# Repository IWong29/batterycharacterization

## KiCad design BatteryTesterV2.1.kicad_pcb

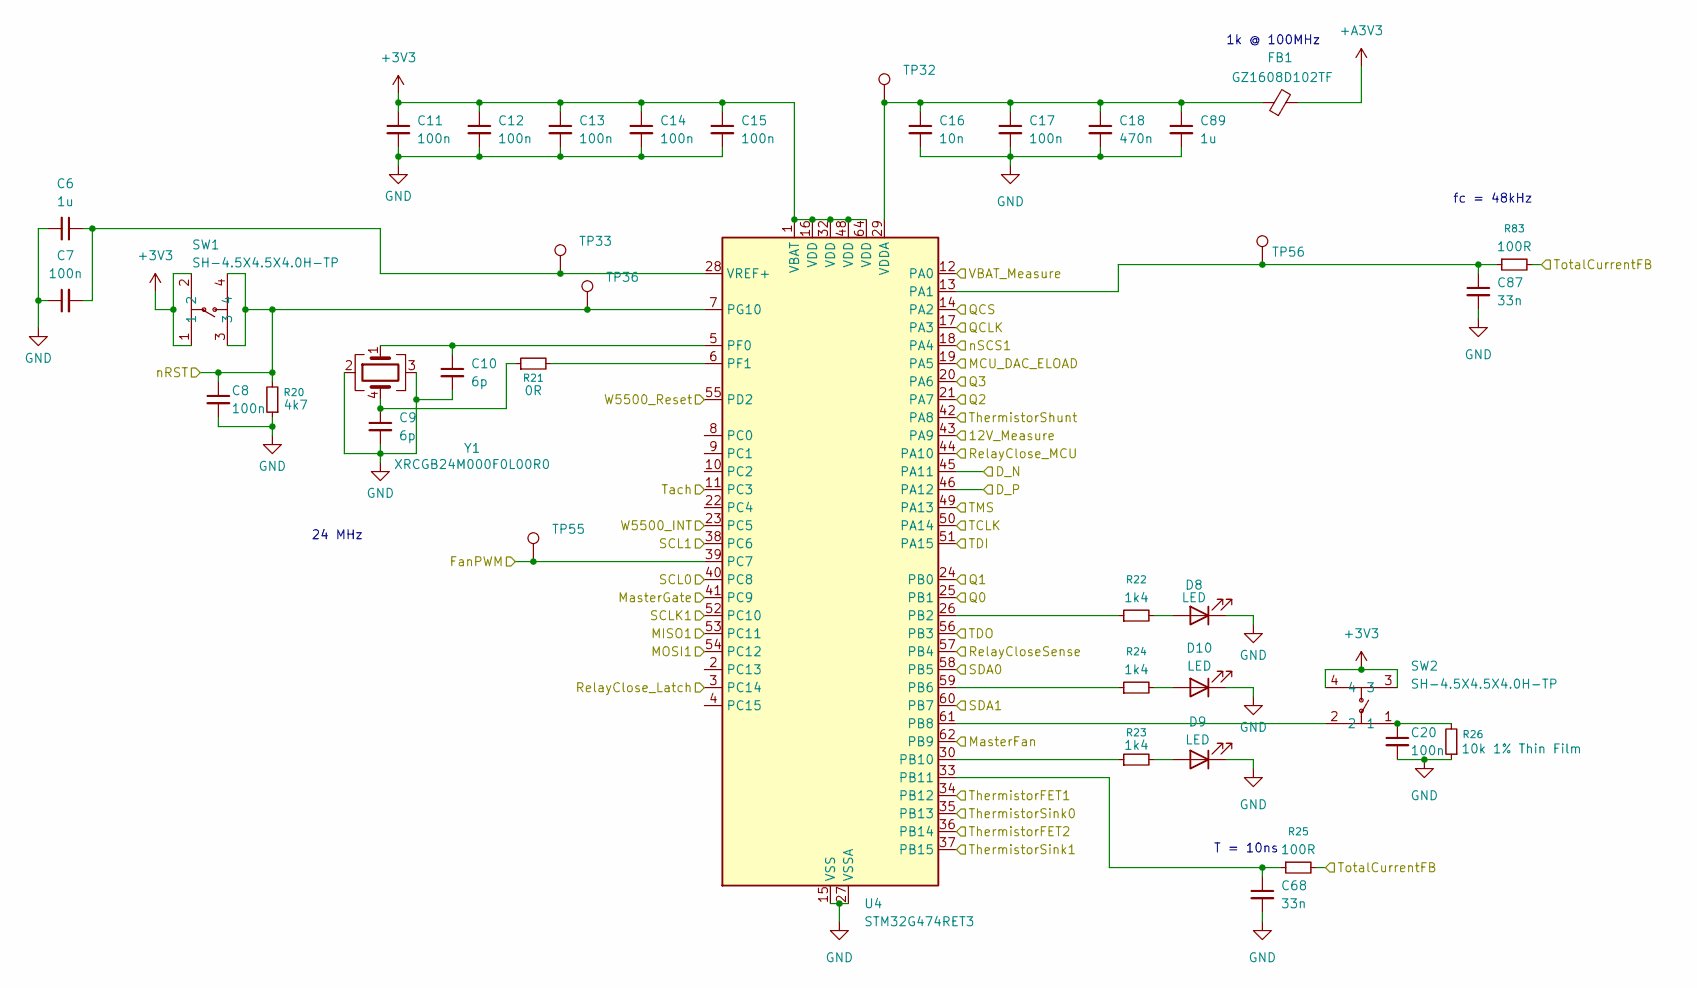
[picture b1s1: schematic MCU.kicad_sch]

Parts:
C6, C89: 1u; C_0603_1608Metric
C7, C11, C12, C13, C14, C15, C17: 100n; C_0603_1608Metric
C8, C20: 100n; C_0402_1005Metric
C9, C10: 6p; C_0402_1005Metric
C16: 10n; C_0603_1608Metric
C18: 470n; C_0603_1608Metric
C68, C87: 33n; C_0603_1608Metric
D8, D9, D10: LED; D_0603_1608Metric
FB1: GZ1608D102TF; C_0603_1608Metric
R20: 4k7; R_0603_1608Metric
R21: 0R; R_0603_1608Metric
R22, R23, R24: 1k4; R_0603_1608Metric
R25, R83: 100R; R_0603_1608Metric
R26: 10k 1% Thin Film; R_0603_1608Metric
SW1, SW2: SH-4.5X4.5X4.0H-TP; SW-SMD_4P-SH-4.5X4.5X4.0H-TP; MPN SH-4.5x4.5x4.0H-TP; LCSC Part C52092029
TP32, TP33, TP36, TP55, TP56: TestPoint; TestPoint_Pad_D1.0mm
U4: STM32G474RET3; LQFP-64_10x10mm_P0.5mm
Y1: XRCGB24M000F0L00R0

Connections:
+3V3: C11.1, C12.1, C13.1, C14.1, C15.1, SW1.1, SW1.2, SW2.3, SW2.4, U4.1 (VBAT), U4.16 (VDD), U4.32 (VDD), U4.48 (VDD), U4.64 (VDD); also elsewhere on the board
+A3V3: FB1.2; also elsewhere on the board
/BatteryV2/MasterGate: U4.41 (PC9); also elsewhere on the board
/BatteryV2/RelayCloseOut: U4.57 (PB4); also elsewhere on the board
/BatteryV2/RelayClose_Latch: U4.3 (PC14); also elsewhere on the board
/BatteryV2/RelayClose_MCU: U4.44 (PA10); also elsewhere on the board
/Connectors/D_N: U4.45 (PA11); also elsewhere on the board
/Connectors/D_P: U4.46 (PA12); also elsewhere on the board
/Connectors/Fan_PWM: TP55.1, U4.39 (PC7); also elsewhere on the board
/Connectors/MasterFan: U4.62 (PB9); also elsewhere on the board
/Connectors/TCLK: U4.50 (PA14); also elsewhere on the board
/Connectors/TDI: U4.51 (PA15); also elsewhere on the board
/Connectors/TDO: U4.56 (PB3); also elsewhere on the board
/Connectors/TMS: U4.49 (PA13); also elsewhere on the board
/Connectors/Tach: U4.11 (PC3); also elsewhere on the board
/Connectors/nRST: C8.1, R20.2, SW1.3, SW1.4, TP36.1, U4.7 (PG10); also elsewhere on the board
/ELOAD/MCU_DAC_ELOAD: U4.19 (PA5); also elsewhere on the board
/ELOAD/ThermistorSink0: U4.35 (PB13); also elsewhere on the board
/ELOAD/ThermistorSink1: U4.37 (PB15); also elsewhere on the board
/MCU/12V_Measure: U4.43 (PA9); also elsewhere on the board
/MCU/MISO1: U4.53 (PC11); also elsewhere on the board
/MCU/MOSI1: U4.54 (PC12); also elsewhere on the board
/MCU/Q0: U4.25 (PB1); also elsewhere on the board
/MCU/Q1: U4.24 (PB0); also elsewhere on the board
/MCU/Q2: U4.21 (PA7); also elsewhere on the board
/MCU/Q3: U4.20 (PA6); also elsewhere on the board
/MCU/QCLK: U4.17 (PA3); also elsewhere on the board
/MCU/QCS: U4.14 (PA2); also elsewhere on the board
/MCU/SCL0: U4.40 (PC8)
/MCU/SCL1: U4.38 (PC6); also elsewhere on the board
/MCU/SCLK1: U4.52 (PC10); also elsewhere on the board
/MCU/SDA0: U4.58 (PB5)
/MCU/SDA1: U4.60 (PB7); also elsewhere on the board
/MCU/ThermistorFET1: U4.34 (PB12); also elsewhere on the board
/MCU/ThermistorFET2: U4.36 (PB14); also elsewhere on the board
/MCU/ThermistorShunt: U4.42 (PA8); also elsewhere on the board
/MCU/TotalCurrentFB: R25.2, R83.2; also elsewhere on the board
/MCU/VBAT_Measure: U4.12 (PA0); also elsewhere on the board
/MCU/W5500_INT: U4.23 (PC5); also elsewhere on the board
/MCU/W5500_Reset: U4.55 (PD2); also elsewhere on the board
/MCU/nSCS1: U4.18 (PA4); also elsewhere on the board
GND: C6.2, C7.1, C8.2, C9.2, C10.2, C11.2, C12.2, C13.2, C14.2, C15.2, C16.2, C17.2, C18.2, C20.2, C68.2, C87.2, C89.2, D8.1 (K), D9.1 (K), D10.1 (K), R20.1, R26.1, U4.15 (VSS), U4.27 (VSSA), U4.31 (VSS), U4.47 (VSS), U4.63 (VSS), Y1.2, Y1.3; also elsewhere on the board
unnamed: C9.1, R21.1, Y1.4
unnamed: C20.1, R26.2, SW2.1
unnamed: D8.2 (A), R22.2
unnamed: D9.2 (A), R23.2
unnamed: D10.2 (A), R24.2
unnamed: C87.1, R83.1, TP56.1, U4.13 (PA1)
unnamed: R22.1, U4.26 (PB2)
unnamed: R24.1, U4.59 (PB6)
unnamed: SW2.2, U4.61 (PB8)
unnamed: R23.1, U4.30 (PB10)
unnamed: C68.1, R25.1, U4.33 (PB11)
unnamed: C10.1, U4.5 (PF0), Y1.1
unnamed: R21.2, U4.6 (PF1)
unnamed: C16.1, C17.1, C18.1, C89.1, FB1.1, TP32.1, U4.29 (VDDA)
unnamed: C6.1, C7.2, TP33.1, U4.28 (VREF+)

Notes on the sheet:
24 MHz
fc = 48kHz
T = 10ns
1k @ 100MHz

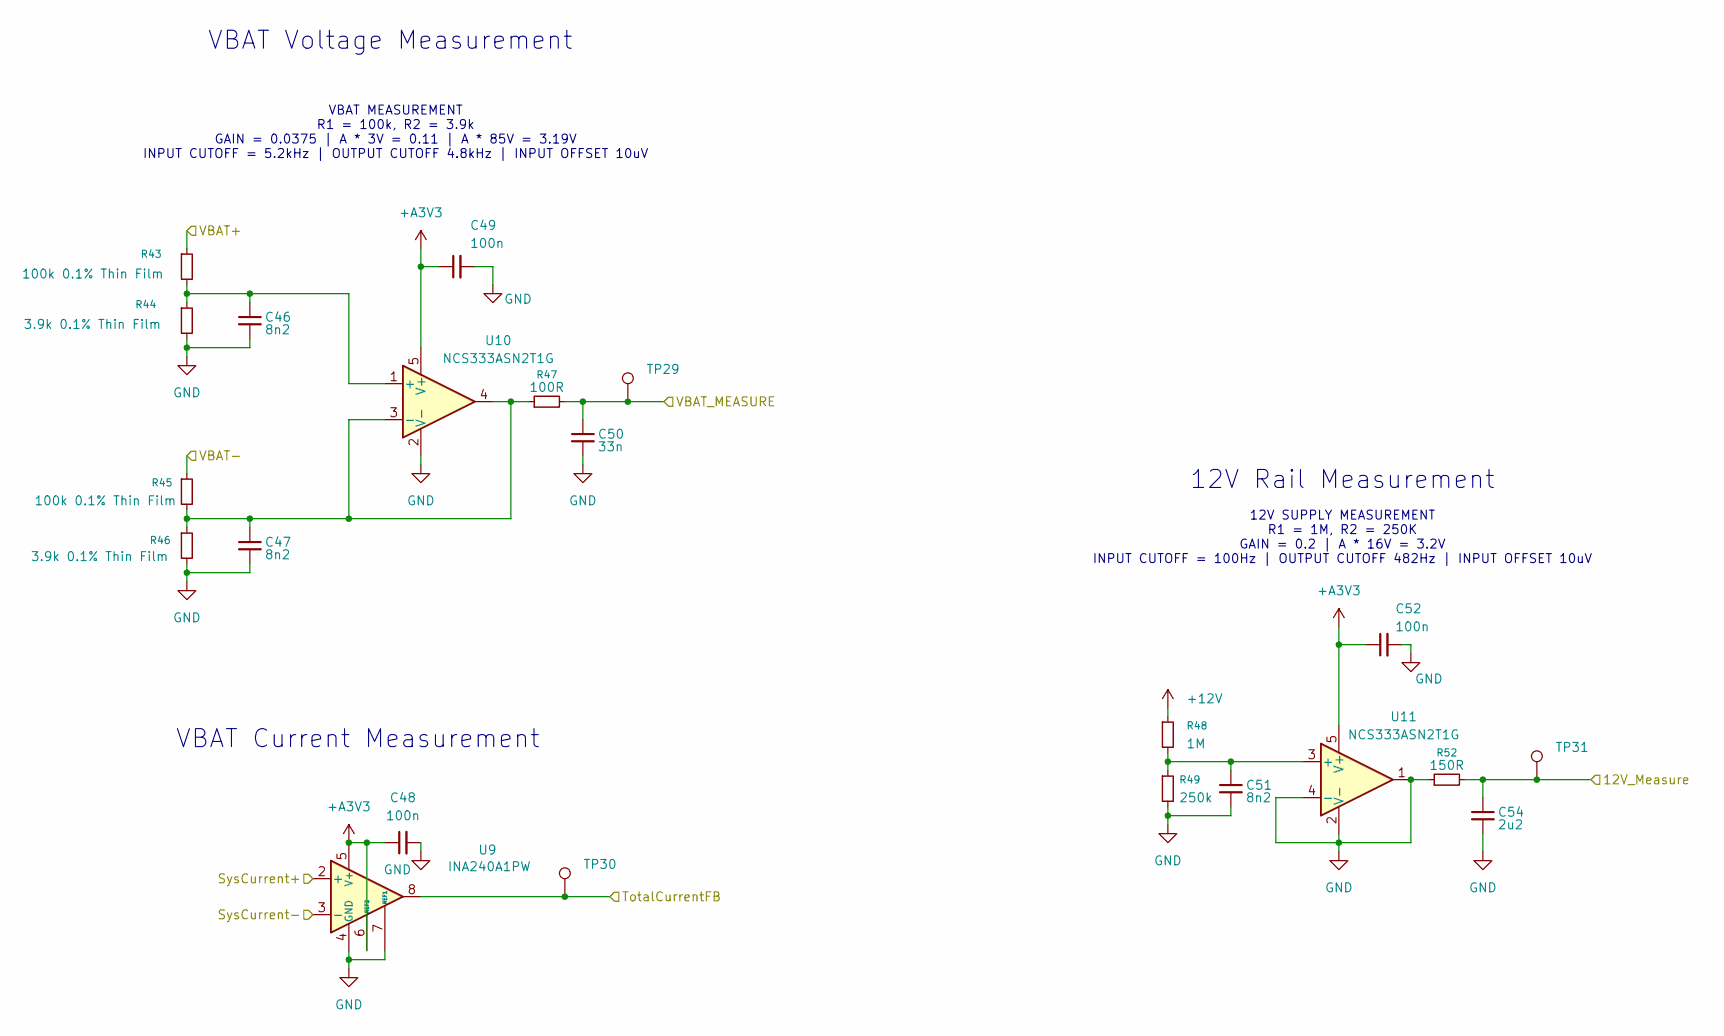
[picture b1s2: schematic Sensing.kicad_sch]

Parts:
C46, C47, C51: 8n2; C_0603_1608Metric
C48, C49, C52: 100n; C_0603_1608Metric
C50: 33n; C_0603_1608Metric
C54: 2u2; C_0603_1608Metric
R43, R45: 100k 0.1% Thin Film; C_1206_3216Metric
R44, R46: 3.9k 0.1% Thin Film; C_1206_3216Metric
R47: 100R; R_0603_1608Metric
R48: 1M; C_1206_3216Metric
R49: 250k; C_1206_3216Metric
R52: 150R; R_0603_1608Metric
TP29, TP30, TP31: TestPoint; TestPoint_Pad_D1.0mm
U9: INA240A1PW; TSSOP-8_4.4x3mm_P0.65mm
U10, U11: NCS333ASN2T1G; SOT-23-5_HandSoldering

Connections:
+12V: R48.1; also elsewhere on the board
+A3V3: C48.1, C49.1, C52.1, U9.5 (V+), U9.6 (REF2), U10.5 (V+), U11.5 (V+); also elsewhere on the board
+VBAT: R43.1; also elsewhere on the board
-BATT: R45.1; also elsewhere on the board
/BatteryV2/SysCurrent+: U9.2 (+); also elsewhere on the board
/BatteryV2/SysCurrent-: U9.3 (-); also elsewhere on the board
/MCU/12V_Measure: C54.1, R52.2, TP31.1; also elsewhere on the board
/MCU/TotalCurrentFB: TP30.1, U9.8; also elsewhere on the board
/MCU/VBAT_Measure: C50.1, R47.2, TP29.1; also elsewhere on the board
GND: C46.2, C47.2, C48.2, C49.2, C50.2, C51.2, C52.2, C54.2, R44.2, R46.2, R49.2, R52.1, U9.1 (GND), U9.4 (GND), U9.7 (REF1), U10.2 (V-), U11.1, U11.2 (V-), U11.4 (-); also elsewhere on the board
unnamed: C46.1, R43.2, R44.1, U10.1 (+)
unnamed: C47.1, R45.2, R46.1, R47.1, U10.3 (-), U10.4
unnamed: C51.1, R48.2, R49.1, U11.3 (+)

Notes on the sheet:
12V Rail Measurement
VBAT MEASUREMENT R1 = 100k, R2 = 3.9k GAIN = 0.0375 | A * 3V = 0.11 | A * 85V = 3.19V INPUT CUTOFF = 5.2kHz | OUTPUT CUTOFF 4.8kHz | INPUT OFFSET 10uV
12V SUPPLY MEASUREMENT R1 = 1M, R2 = 250K GAIN = 0.2 | A * 16V = 3.2V INPUT CUTOFF = 100Hz | OUTPUT CUTOFF 482Hz | INPUT OFFSET 10uV
VBAT Voltage Measurement
VBAT Current Measurement

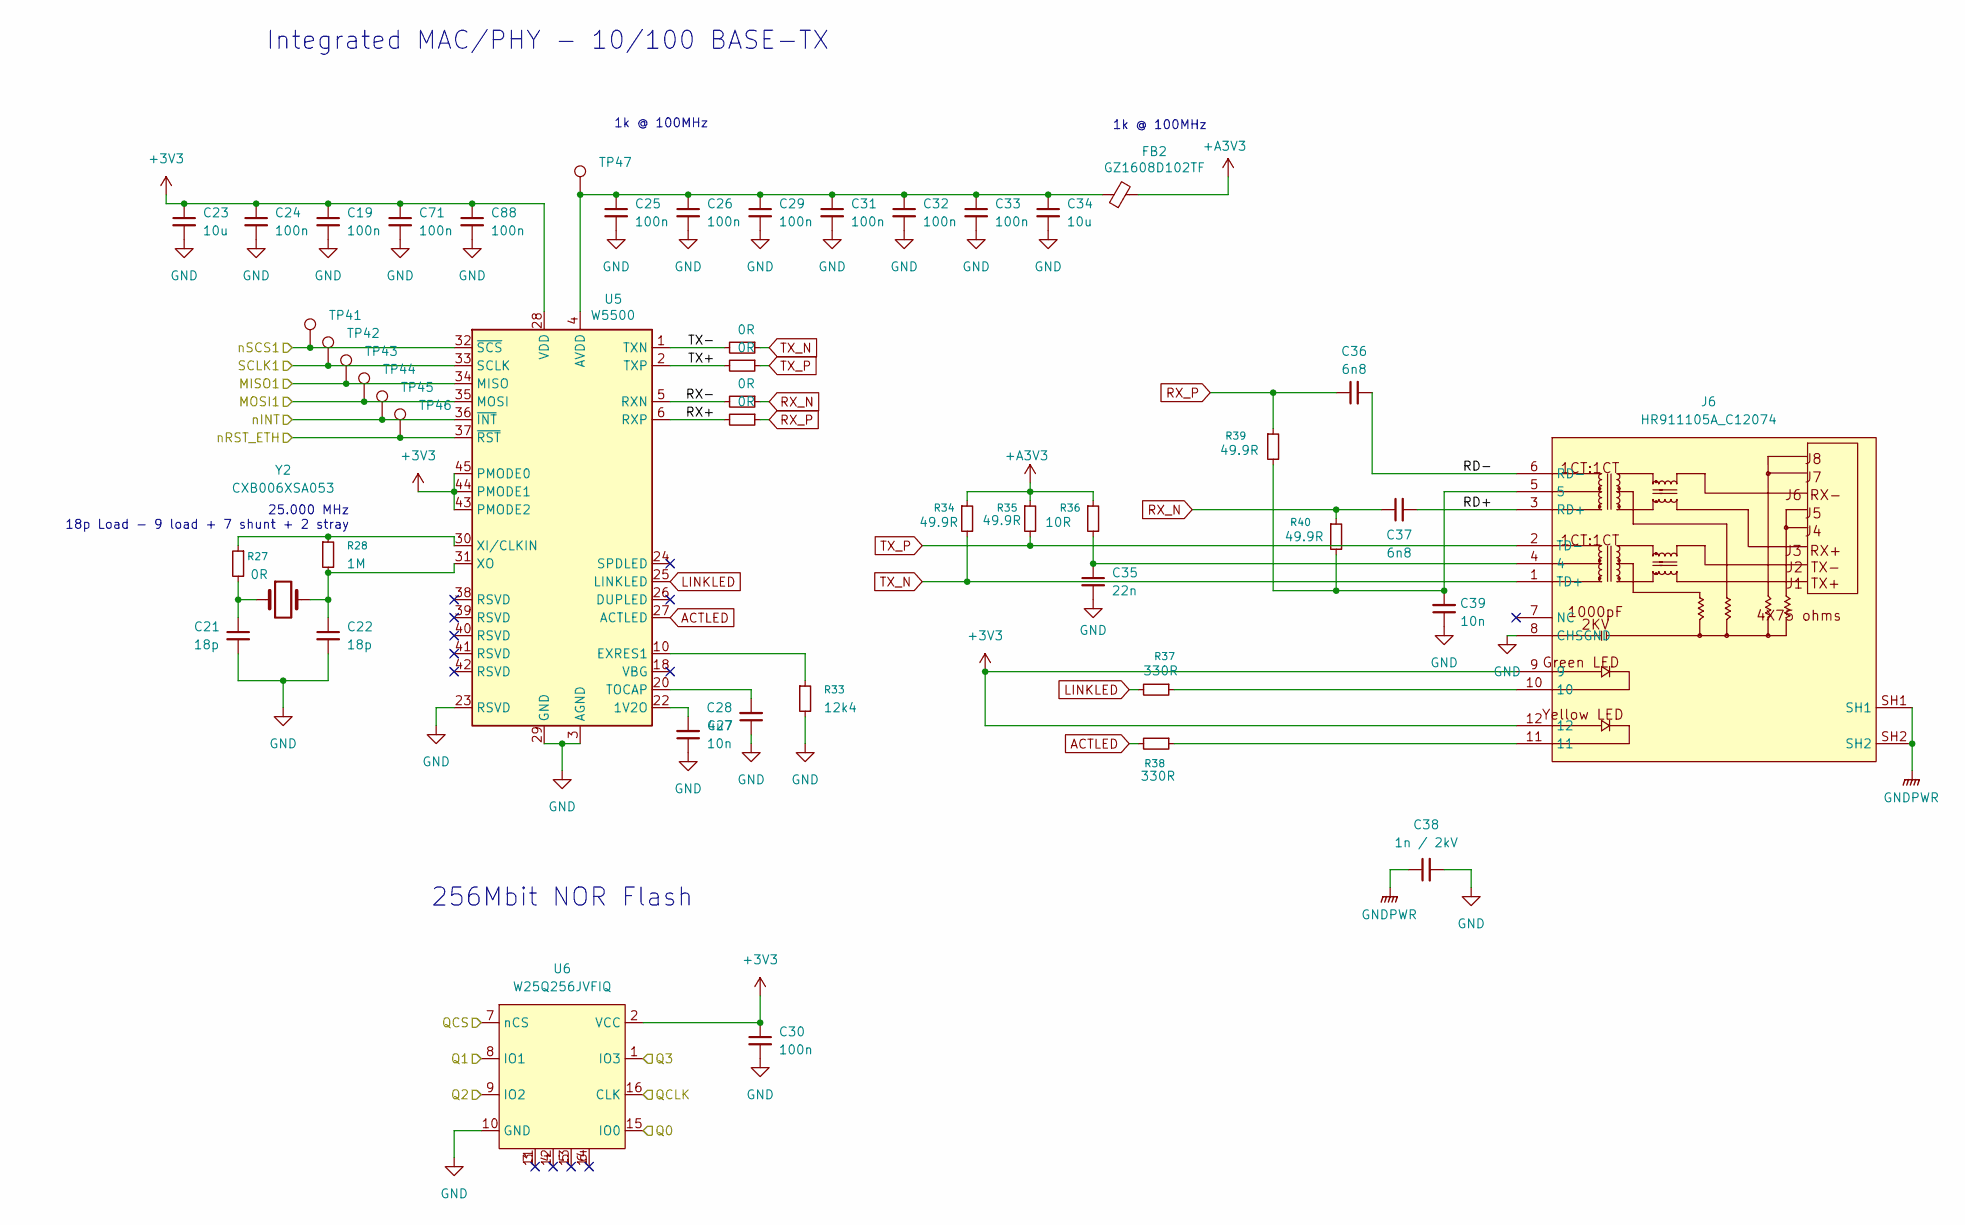
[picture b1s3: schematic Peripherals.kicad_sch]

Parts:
C19, C24, C25, C26, C29, C30, C31, C32, C33, C71, C88: 100n; C_0603_1608Metric
C21, C22: 18p; C_0402_1005Metric
C23, C34: 10u; C_1206_3216Metric
C27, C39: 10n; C_0603_1608Metric
C28: 4u7; C_0805_2012Metric
C35: 22n; C_0603_1608Metric
C36, C37: 6n8; C_0603_1608Metric
C38: 1n / 2kV; C_1206_3216Metric
FB2: GZ1608D102TF; C_0603_1608Metric
J6: HR911105A_C12074; RJ45-TH_HR911105A; MPN HR911105A; LCSC Part C12074
R27, R29, R30, R31, R32: 0R; R_0603_1608Metric
R28: 1M; C_1206_3216Metric
R33: 12k4; R_0603_1608Metric
R34, R35, R39, R40: 49.9R; R_0603_1608Metric
R36: 10R; R_0603_1608Metric
R37, R38: 330R; R_0603_1608Metric
TP41, TP42, TP43, TP44, TP45, TP46, TP47: TestPoint; TestPoint_Pad_D1.0mm
U5: W5500; LQFP-48_7x7mm_P0.5mm
U6: W25Q256JVFIQ; SOIC-16_3.9x9.9mm_P1.27mm
Y2: CXB006XSA053; Crystal_SMD_HC49-SD

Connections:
+3V3: C19.1, C23.1, C24.1, C30.1, C71.1, C88.1, J6.9, J6.12, U5.28 (VDD), U5.43 (PMODE2), U5.44 (PMODE1), U5.45 (PMODE0), U6.2 (VCC); also elsewhere on the board
+A3V3: FB2.2, R34.1, R35.1, R36.1; also elsewhere on the board
/MCU/MISO1: TP43.1, U5.34 (MISO); also elsewhere on the board
/MCU/MOSI1: TP44.1, U5.35 (MOSI); also elsewhere on the board
/MCU/Q0: U6.15 (IO0); also elsewhere on the board
/MCU/Q1: U6.8 (IO1); also elsewhere on the board
/MCU/Q2: U6.9 (IO2); also elsewhere on the board
/MCU/Q3: U6.1 (IO3); also elsewhere on the board
/MCU/QCLK: U6.16 (CLK); also elsewhere on the board
/MCU/QCS: U6.7 (nCS); also elsewhere on the board
/MCU/SCLK1: TP42.1, U5.33 (SCLK); also elsewhere on the board
/MCU/W5500_INT: TP45.1, U5.36 (~INT); also elsewhere on the board
/MCU/W5500_Reset: TP46.1, U5.37 (~RST); also elsewhere on the board
/MCU/nSCS1: TP41.1, U5.32 (~SCS); also elsewhere on the board
/Peripherals/RD+: C37.2, J6.3 (RD+)
/Peripherals/RD-: C36.2, J6.6 (RD-)
/Peripherals/RX+: R32.2, U5.6 (RXP)
/Peripherals/RX-: R31.2, U5.5 (RXN)
/Peripherals/TX+: R30.2, U5.2 (TXP)
/Peripherals/TX-: R29.2, U5.1 (TXN)
ACTLED: R38.2, U5.27 (ACTLED)
GND: C19.2, C21.2, C22.2, C23.2, C24.2, C25.2, C26.2, C27.1, C28.1, C29.2, C30.2, C31.2, C32.2, C33.2, C34.2, C35.2, C38.2, C39.1, C71.2, C88.2, J6.8 (CHSGND), R33.2, U5.3 (AGND), U5.9 (AGND), U5.14 (AGND), U5.16 (AGND), U5.19 (AGND), U5.23 (RSVD), U5.29 (GND), U5.48 (AGND), U6.10 (GND); also elsewhere on the board
GNDPWR: C38.1, J6.SH1, J6.SH2
LINKLED: R37.2, U5.25 (LINKLED)
unnamed: C21.1, R27.2, Y2.1
unnamed: C25.1, C26.1, C29.1, C31.1, C32.1, C33.1, C34.1, FB2.1, TP47.1, U5.4 (AVDD), U5.8 (AVDD), U5.11 (AVDD), U5.15 (AVDD), U5.17 (AVDD), U5.21 (AVDD)
unnamed: C35.1, J6.4, R36.2
unnamed: C39.2, J6.5, R39.2, R40.2
unnamed: J6.10, R37.1
unnamed: J6.11, R38.1
unnamed: C27.2, U5.22 (1V2O)
unnamed: R33.1, U5.10 (EXRES1)
unnamed: C28.2, U5.20 (TOCAP)
unnamed: R27.1, R28.1, U5.30 (XI/CLKIN)
unnamed: C22.1, R28.2, U5.31 (XO), Y2.2
RX_N: C37.1, R31.1, R40.1
RX_P: C36.1, R32.1, R39.1
TX_N: J6.1 (TD+), R29.1, R34.2
TX_P: J6.2 (TD-), R30.1, R35.2

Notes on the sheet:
1k @ 100MHz
Integrated MAC/PHY - 10/100 BASE-TX
256Mbit NOR Flash
25.000 MHz 18p Load - 9 load + 7 shunt + 2 stray

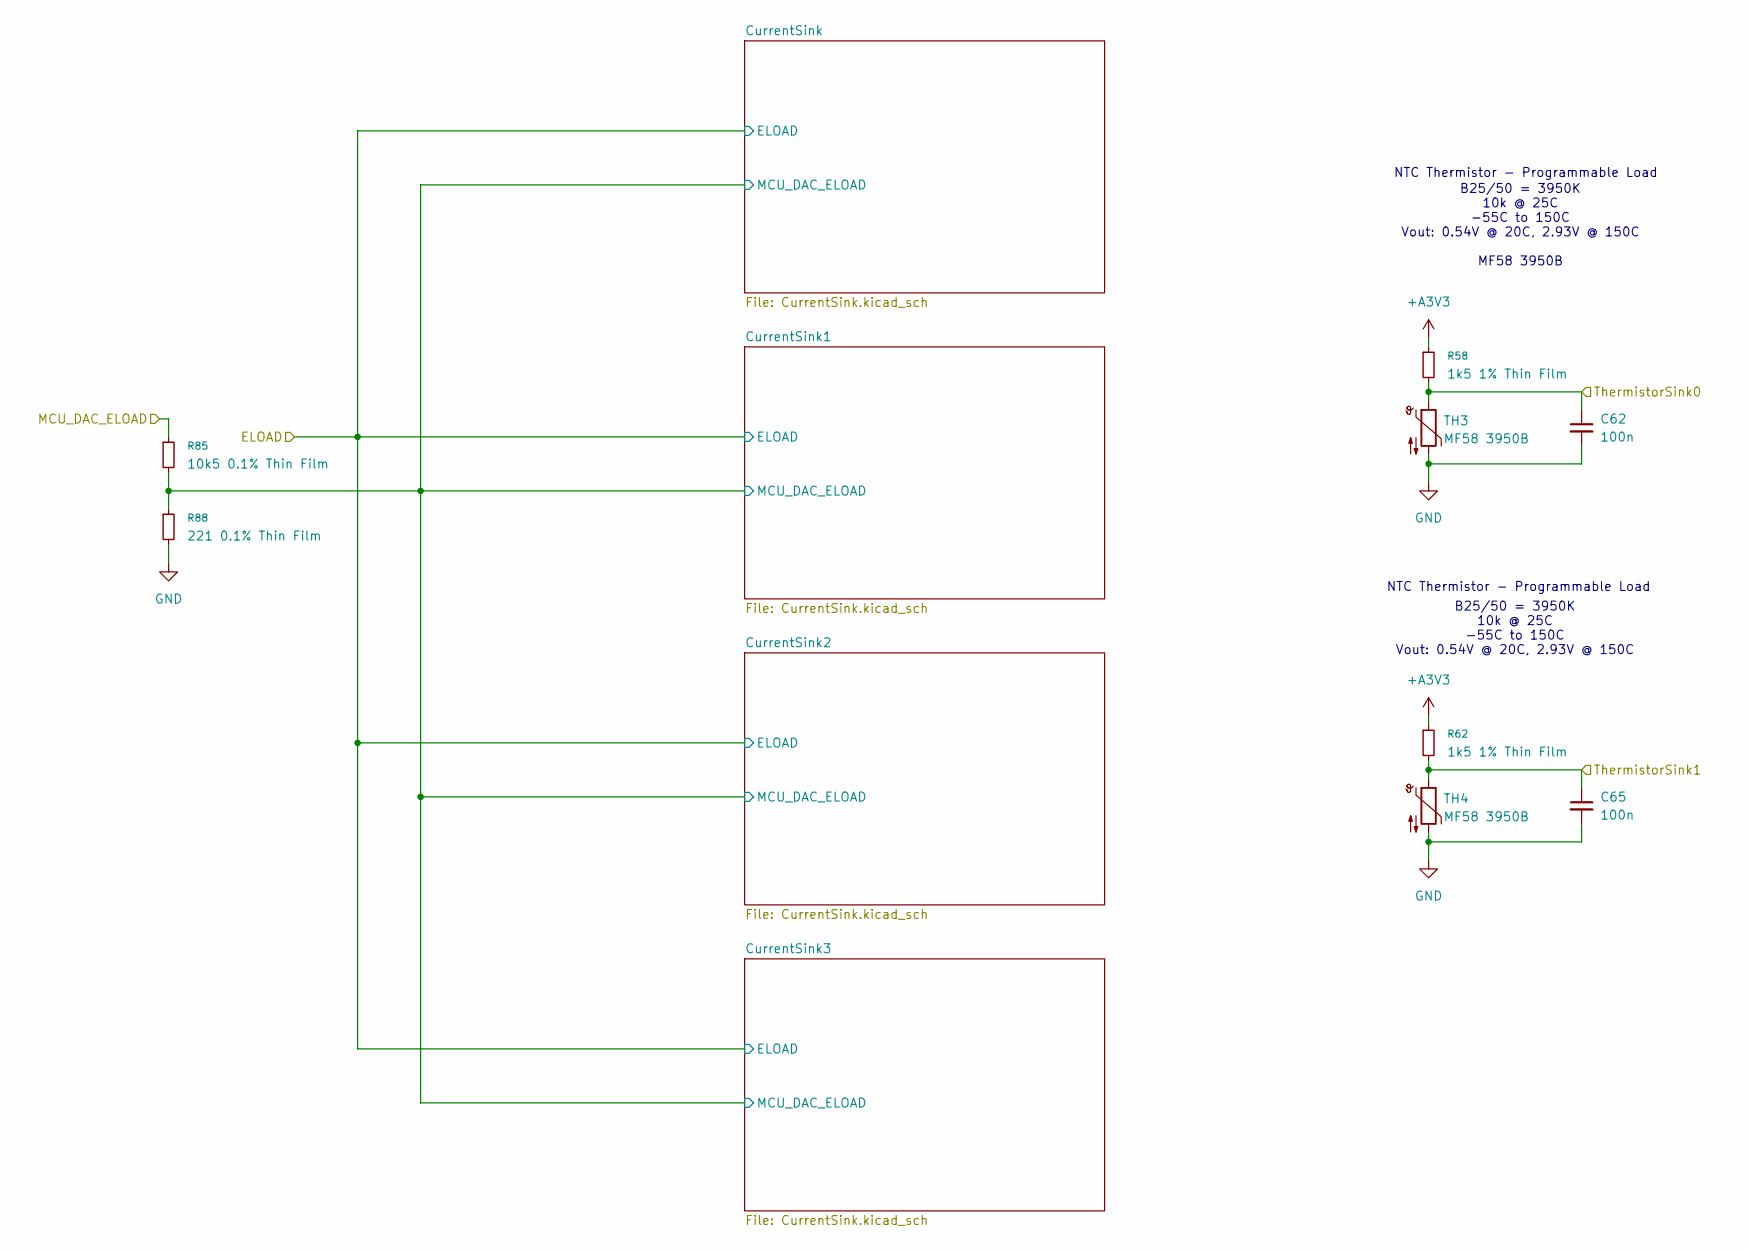
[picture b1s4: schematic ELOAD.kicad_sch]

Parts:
C62, C65: 100n; C_0603_1608Metric
R58, R62: 1k5 1% Thin Film; R_0603_1608Metric
R85: 10k5 0.1% Thin Film; R_0603_1608Metric
R88: 221 0.1% Thin Film; R_0603_1608Metric
TH3, TH4: MF58 3950B; R_Axial_DIN0204_L3.6mm_D1.6mm_P5.08mm_Vertical

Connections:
+A3V3: R58.1, R62.1; also elsewhere on the board
/ELOAD/CurrentSink/MCU_DAC_ELOAD: R85.2, R88.1; also elsewhere on the board
/ELOAD/MCU_DAC_ELOAD: R85.1; also elsewhere on the board
/ELOAD/ThermistorSink0: C62.1, R58.2, TH3.1; also elsewhere on the board
/ELOAD/ThermistorSink1: C65.1, R62.2, TH4.1; also elsewhere on the board
GND: C62.2, C65.2, R88.2, TH3.2, TH4.2; also elsewhere on the board

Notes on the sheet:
B25/50 = 3950K 10k @ 25C -55C to 150C Vout: 0.54V @ 20C, 2.93V @ 150C
NTC Thermistor - Programmable Load
B25/50 = 3950K 10k @ 25C -55C to 150C Vout: 0.54V @ 20C, 2.93V @ 150C MF58 3950B

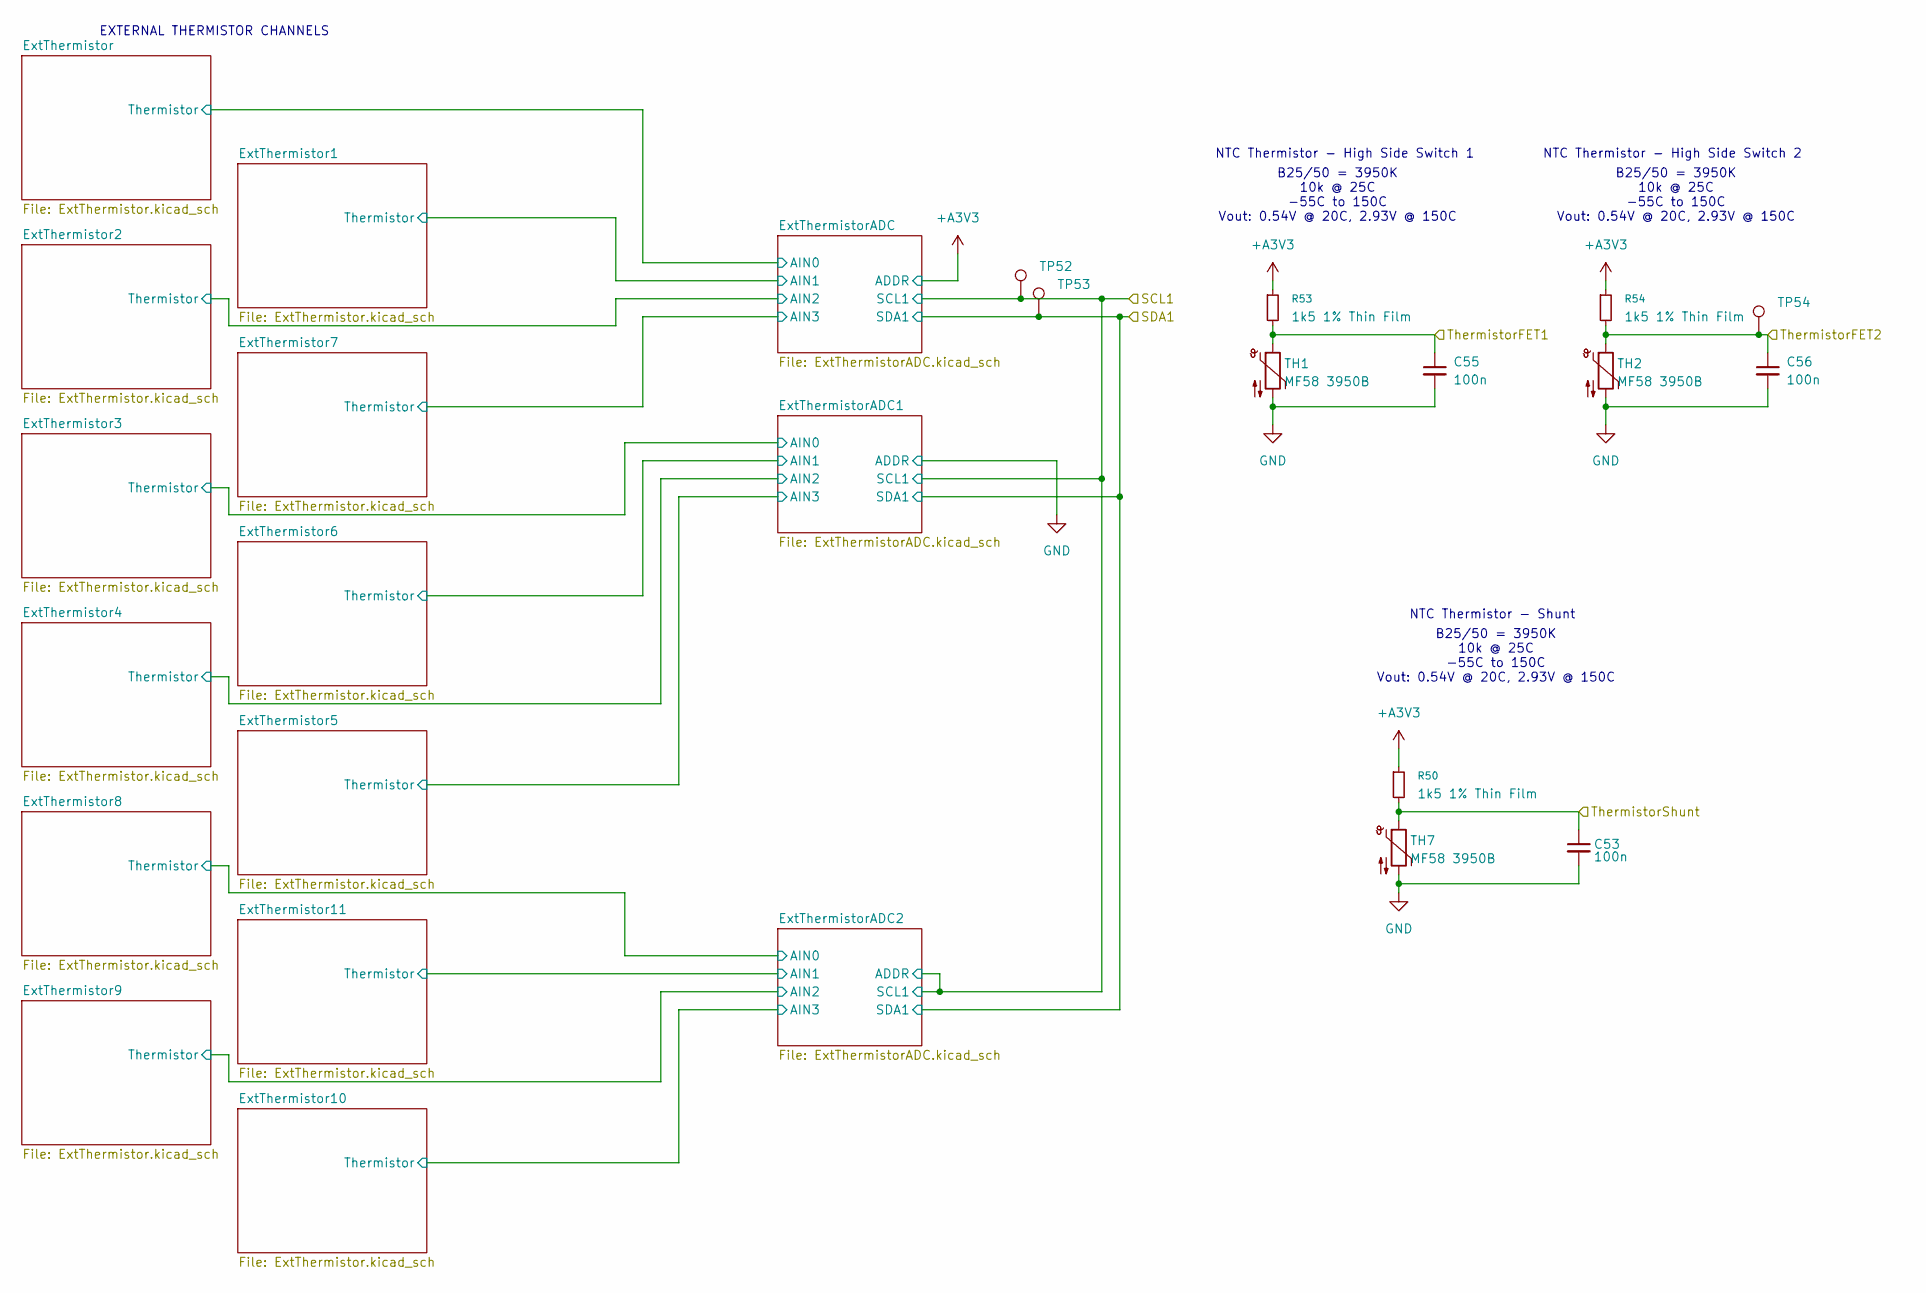
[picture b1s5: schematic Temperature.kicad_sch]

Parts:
C53, C55, C56: 100n; C_0603_1608Metric
R50, R53, R54: 1k5 1% Thin Film; R_0603_1608Metric
TH1, TH2, TH7: MF58 3950B; R_Axial_DIN0204_L3.6mm_D1.6mm_P5.08mm_Vertical
TP52, TP53, TP54: TestPoint; TestPoint_Pad_D1.0mm

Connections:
+A3V3: R50.1, R53.1, R54.1; also elsewhere on the board
/MCU/SCL1: TP52.1; also elsewhere on the board
/MCU/SDA1: TP53.1; also elsewhere on the board
/MCU/ThermistorFET1: C55.1, R53.2, TH1.1; also elsewhere on the board
/MCU/ThermistorFET2: C56.1, R54.2, TH2.1, TP54.1; also elsewhere on the board
/MCU/ThermistorShunt: C53.1, R50.2, TH7.1; also elsewhere on the board
GND: C53.2, C55.2, C56.2, TH1.2, TH2.2, TH7.2; also elsewhere on the board

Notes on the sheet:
NTC Thermistor - Shunt
B25/50 = 3950K 10k @ 25C -55C to 150C Vout: 0.54V @ 20C, 2.93V @ 150C
NTC Thermistor - High Side Switch 2
EXTERNAL THERMISTOR CHANNELS
NTC Thermistor - High Side Switch 1

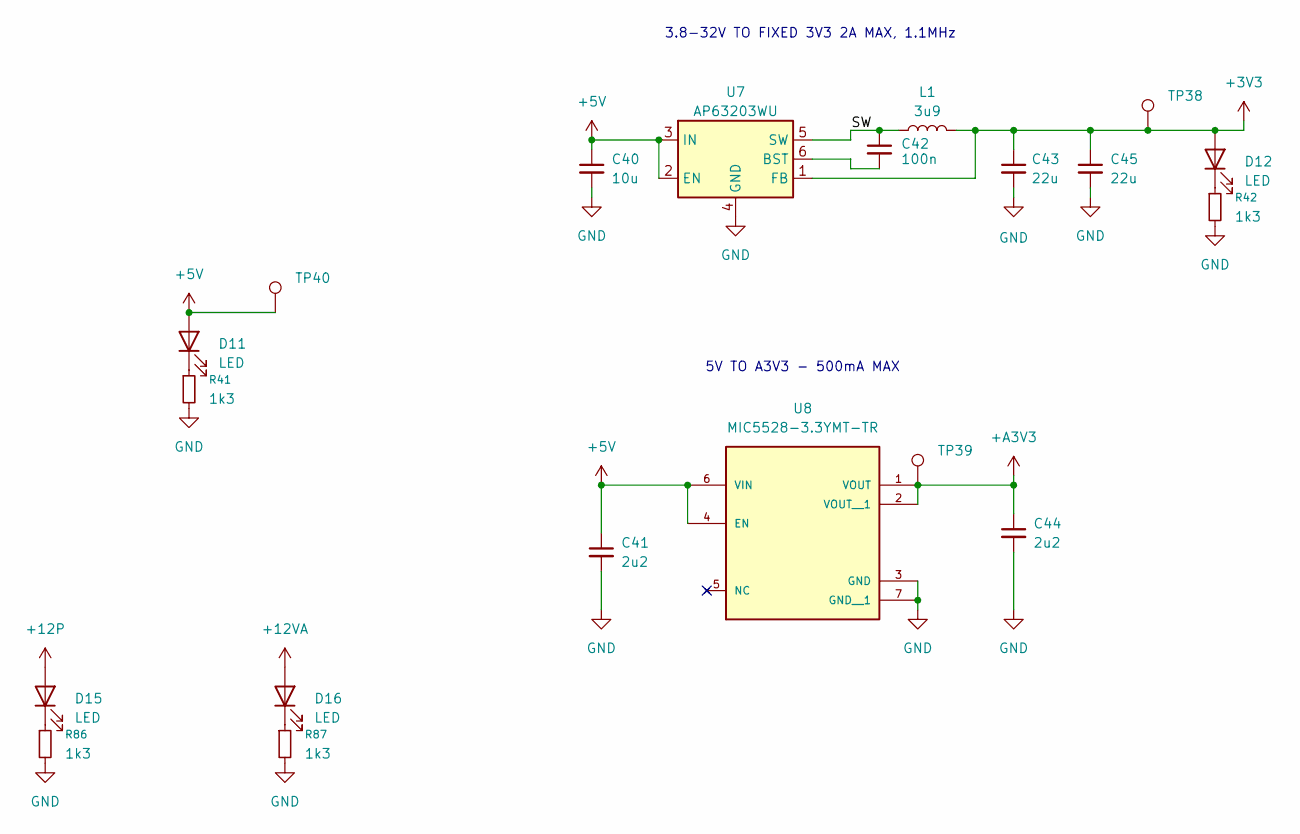
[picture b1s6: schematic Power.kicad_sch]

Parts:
C40: 10u; C_1206_3216Metric
C41, C44: 2u2; C_0603_1608Metric
C42: 100n; C_0603_1608Metric
C43, C45: 22u; C_1206_3216Metric
D11, D12, D15, D16: LED; D_0603_1608Metric
L1: 3u9; Inductor6.3_5.7_2
R41, R42, R86, R87: 1k3; R_0603_1608Metric
TP38, TP39, TP40: TestPoint; TestPoint_Pad_D1.0mm
U7: AP63203WU; TSOT-23-6
U8: MIC5528-3.3YMT-TR; TDFN-6-1EP_1.2x1.2mm_P0.4mm_EP0.3x0.94mm

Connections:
+3V3: C43.1, C45.1, D12.2 (A), L1.2, TP38.1, U7.1 (FB); also elsewhere on the board
+5V: C40.1, C41.1, D11.2 (A), TP40.1, U7.2 (EN), U7.3 (IN), U8.4 (EN), U8.6 (VIN); also elsewhere on the board
+12P: D15.2 (A); also elsewhere on the board
+12VA: D16.2 (A); also elsewhere on the board
+A3V3: C44.1, TP39.1, U8.1 (VOUT), U8.2 (VOUT__1); also elsewhere on the board
/Power/SW: C42.1, L1.1, U7.5 (SW)
GND: C40.2, C41.2, C43.2, C44.2, C45.2, R41.2, R42.2, R86.2, R87.2, U7.4 (GND), U8.3 (GND), U8.7 (GND__1); also elsewhere on the board
unnamed: D11.1 (K), R41.1
unnamed: D12.1 (K), R42.1
unnamed: D15.1 (K), R86.1
unnamed: D16.1 (K), R87.1
unnamed: C42.2, U7.6 (BST)

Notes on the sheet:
5V TO A3V3 - 500mA MAX
3.8-32V TO FIXED 3V3 2A MAX, 1.1MHz
